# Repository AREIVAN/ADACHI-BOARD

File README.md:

# ADACHI-BOARD  
### Custom Embedded Control Board for Mini Sumo Robotics  
**ESP32-S3 | PCB Design | Motor Control | Embedded Systems**

---

## 📍 Overview

**ADACHI-BOARD** is a **custom-designed embedded control board** developed for **Mini Sumo robotic applications**, focused on **real-time control**, **compact PCB design**, and **competition-grade reliability**.

This project was created as part of my professional and academic development in **Robotics, Embedded Systems, and Industrial Electronics**, and it is intended to serve as both a **functional robotic platform** and a **technical portfolio project**.

---

## 🎯 Project Objectives

- Design a **compact and robust PCB** for competitive robotics
- Implement **reliable motor control** using discrete drivers
- Apply **best practices in embedded hardware design**
- Demonstrate skills in:
  - PCB design
  - Power regulation
  - Microcontroller integration
  - Robotics-oriented system architecture

---

## ⚙️ System Architecture

- **Main MCU:** ESP32-S3 Mini-1U  
- **Motor Control:** Dual DRV8871 DC motor drivers  
- **Sensors:** Support for up to 10 external sensors  
- **Actuators:** 2 servo outputs  
- **User Interface:** Hardware buttons for strategy selection  
- **Programming Interface:** TTL (UART)  

The board is designed to minimize latency and allow fast response times, which are critical in competitive robotics environments.

---

## 📐 Technical Specifications

| Feature | Description |
|------|------------|
| Board Size | 60 mm × 30 mm |
| Max Input Voltage | 24 V |
| MCU | ESP32-S3 Mini-1U |
| Motor Drivers | DRV8871 |
| Voltage Regulation | 5 V / 3.3 V |
| LEDs | SK0605 2427 |
| Programming | UART (TTL) |
| Target Application | Mini Sumo Robot |

---

## 🔘 Hardware Controls

- **RESET** – Microcontroller reset  
- **BOOT** – Programming mode access  
- **STRATEGY 1** – Strategy selection input  
- **STRATEGY 2** – Strategy selection input  

These buttons allow strategy changes without reflashing firmware, improving usability during competitions or testing.

---

## 🧠 Design Considerations

- Compact footprint optimized for Mini Sumo chassis
- Separation of power and logic domains
- Component selection focused on availability and reliability
- Design prepared for iterative improvement and future expansion

---

## 📂 Repository Structure

*(Structure may evolve as the project progresses)*

---

## 🚧 Project Status

- ✔ PCB design completed  
- ✔ Component selection validated  
- 🔄 Firmware development in progress  
- 🔄 Testing and optimization phase  

---

## 🔮 Planned Improvements

- Encoder feedback integration
- Power efficiency optimization
- Enhanced firmware architecture
- Step-by-step replication documentation
- Optional telemetry and data logging

---

## 👨‍💻 About the Author

**Areivan**  
Industrial Robotics Engineering Student  
Industrial Maintenance Technician  

- Experience in embedded systems and PCB design  
- Background in industrial automation and maintenance  
- Focused on robotics, electronics, and applied engineering  

🔗 GitHub: https://github.com/AREIVAN

---

## 📜 License & Usage

This project is intended for **educational and experimental purposes**.  
You may reference or reuse the design with proper credit to the author.

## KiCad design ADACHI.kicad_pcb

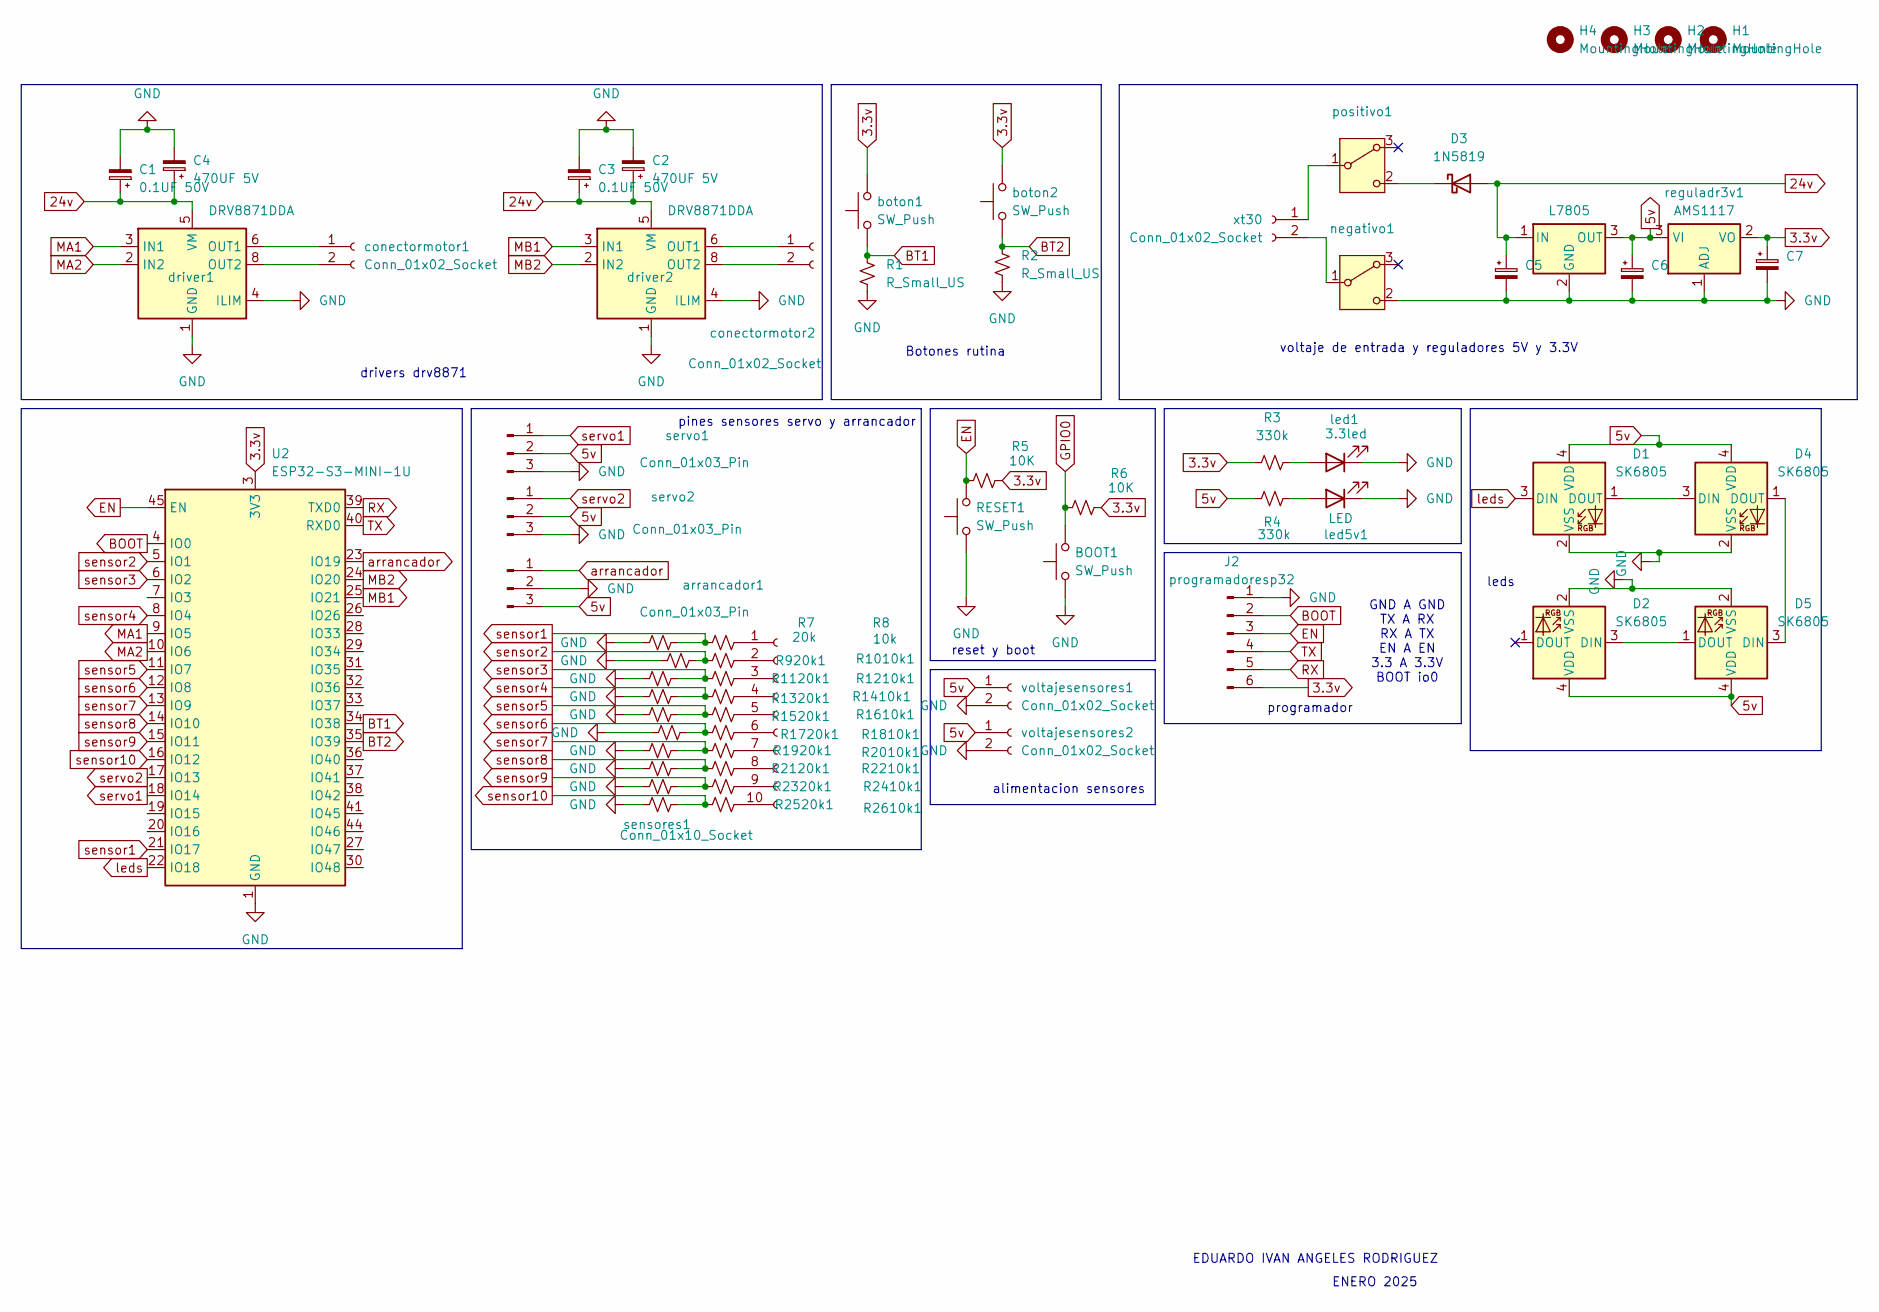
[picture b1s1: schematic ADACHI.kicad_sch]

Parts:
BOOT1: SW_Push; SW_Push_1P1T_NO_Vertical_Wuerth_434133025816
C1, C3: 0.1UF 50V; C_0603_1608Metric
C2, C4: 470UF 5V; C_1210_3225Metric
C5, C6, C7: C_0603_1608Metric
D1, D2, D4, D5: SK6805; LED_SK6805_PLCC4_2.4x2.7mm_P1.3mm
D3: 1N5819; D_DO-41_SOD81_P10.16mm_Horizontal
H1, H3, H4: MountingHole; MountingHole_2.2mm_M2_ISO7380_Pad_TopBottom
H2: MountingHole; MountingHole_2.2mm_M2_ISO14580_Pad_TopBottom
J2: programadoresp32; PinHeader_1x06_P2.54mm_Vertical
R1, R2: R_Small_US; R_0603_1608Metric
R3, R4: 330k; R_0603_1608Metric
R5, R6: 10K; R_0603_1608Metric
R7: 20k; R_0603_1608Metric
R8: 10k; R_0603_1608Metric
R920k1, R1010k1, R1120k1, R1210k1, R1320k1, R1410k1, R1520k1, R1610k1, R1720k1, R1810k1, R1920k1, R2010k1, R2120k1, R2210k1, R2320k1, R2410k1, R2520k1, R2610k1: R_0603_1608Metric
RESET1: SW_Push; SW_Push_1P1T_NO_Vertical_Wuerth_434133025816
U1: L7805; TO-252-2
U2: ESP32-S3-MINI-1U; ESP32-S2-MINI-1U
arrancador1: Conn_01x03_Pin; PinHeader_1x03_P2.54mm_Vertical
boton1, boton2: SW_Push; SW_Push_1P1T_NO_Vertical_Wuerth_434133025816
conectormotor1, conectormotor2: Conn_01x02_Socket; PinSocket_1x02_P2.54mm_Vertical
driver1, driver2: DRV8871DDA; Texas_HTSOP-8-1EP_3.9x4.9mm_P1.27mm_EP2.95x4.9mm_Mask2.4x3.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
led1: 3.3led; LED_0603_1608Metric
led5v1: LED; LED_0603_1608Metric
negativo1: SW_Slide-03_Wuerth-WS-SLTV_10x2.5x6.4_P2.54mm
positivo1: SW_Slide-03_Wuerth-WS-SLTV_10x2.5x6.4_P2.54mm
reguladr3v1: AMS1117; SOT-223-3_TabPin2
sensores1: Conn_01x10_Socket; PinHeader_1x10_P2.54mm_Vertical
servo1, servo2: Conn_01x03_Pin; PinHeader_1x03_P2.54mm_Vertical
voltajesensores1, voltajesensores2: Conn_01x02_Socket; PinHeader_1x02_P2.54mm_Vertical
xt30: Conn_01x02_Socket; PinHeader_1x02_P2.54mm_Vertical

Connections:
3.3v: C7.1, J2.6, R3.1, R5.2, R6.2, U2.3 (3V3), boton1.2, boton2.2, reguladr3v1.2 (VO)
5v: C6.1, D1.4 (VDD), D2.4 (VDD), D4.4 (VDD), D5.4 (VDD), R4.1, U1.3 (OUT), arrancador1.3, reguladr3v1.3 (VI), servo1.2, servo2.2, voltajesensores1.1, voltajesensores2.1
24v: C1.1, C2.1, C3.1, C4.1, C5.1, D3.2 (A), U1.1 (IN), driver1.5 (VM), driver2.5 (VM)
BOOT: J2.2, U2.4 (IO0)
BT1: R1.1, U2.34 (IO38), boton1.1
BT2: R2.1, U2.35 (IO39), boton2.1
EN: J2.3, R5.1, RESET1.2, U2.45 (EN)
GND: BOOT1.1, C1.2, C2.2, C3.2, C4.2, C5.2, C6.2, C7.2, D1.2 (VSS), D2.2 (VSS), D4.2 (VSS), D5.2 (VSS), J2.1, R1.2, R2.2, R7.2, R920k1.2, R1120k1.2, R1320k1.2, R1520k1.2, R1720k1.2, R1920k1.2, R2120k1.2, R2320k1.2, R2520k1.2, RESET1.1, U1.2 (GND), U2.1 (GND), U2.2 (GND), U2.42 (GND), U2.43 (GND), U2.46 (GND), U2.47 (GND), U2.48 (GND), U2.49 (GND), U2.50 (GND), U2.51 (GND), U2.52 (GND), U2.53 (GND), U2.54 (GND), U2.55 (GND), U2.56 (GND), U2.57 (GND), U2.58 (GND), U2.59 (GND), U2.60 (GND), U2.61 (GND), U2.62 (GND), U2.63 (GND), U2.64 (GND), U2.65 (GND), arrancador1.2, driver1.1 (GND), driver1.4 (ILIM), driver1.7 (GND), driver1.9 (GND), driver2.1 (GND), driver2.4 (ILIM), driver2.7 (GND), driver2.9 (GND), led1.1 (K), led5v1.1 (K), negativo1.2 (C), reguladr3v1.1 (ADJ), servo1.3, servo2.3, voltajesensores1.2, voltajesensores2.2
GPIO0: BOOT1.2, R6.1
MA1: U2.9 (IO5), driver1.3 (IN1)
MA2: U2.10 (IO6), driver1.2 (IN2)
MB1: U2.25 (IO21), driver2.3 (IN1)
MB2: U2.24 (IO20), driver2.2 (IN2)
unnamed: D1.1 (DOUT), D4.3 (DIN)
unnamed: D2.3 (DIN), D5.1 (DOUT)
unnamed: D3.1 (K), positivo1.2 (C)
unnamed: D4.1 (DOUT), D5.3 (DIN)
unnamed: conectormotor1.1, driver1.6 (OUT1)
unnamed: conectormotor1.2, driver1.8 (OUT2)
unnamed: conectormotor2.1, driver2.6 (OUT1)
unnamed: conectormotor2.2, driver2.8 (OUT2)
unnamed: R3.2, led1.2 (A)
unnamed: R4.2, led5v1.2 (A)
unnamed: negativo1.1 (B), xt30.2
unnamed: positivo1.1 (B), xt30.1
unnamed: R8.1, sensores1.1
unnamed: R1010k1.1, sensores1.2
unnamed: R1210k1.1, sensores1.3
unnamed: R1410k1.1, sensores1.4
unnamed: R1610k1.1, sensores1.5
unnamed: R1810k1.1, sensores1.6
unnamed: R2010k1.1, sensores1.7
unnamed: R2210k1.1, sensores1.8
unnamed: R2410k1.1, sensores1.9
unnamed: R2610k1.1, sensores1.10
RX: J2.5, U2.39 (TXD0)
TX: J2.4, U2.40 (RXD0)
arrancador: U2.23 (IO19), arrancador1.1
leds: D1.3 (DIN), U2.22 (IO18)
sensor1: R7.1, R8.2, U2.21 (IO17)
sensor2: R920k1.1, R1010k1.2, U2.5 (IO1)
sensor3: R1120k1.1, R1210k1.2, U2.6 (IO2)
sensor4: R1320k1.1, R1410k1.2, U2.8 (IO4)
sensor5: R1520k1.1, R1610k1.2, U2.11 (IO7)
sensor6: R1720k1.1, R1810k1.2, U2.12 (IO8)
sensor7: R1920k1.1, R2010k1.2, U2.13 (IO9)
sensor8: R2120k1.1, R2210k1.2, U2.14 (IO10)
sensor9: R2320k1.1, R2410k1.2, U2.15 (IO11)
sensor10: R2520k1.1, R2610k1.2, U2.16 (IO12)
servo1: U2.18 (IO14), servo1.1
servo2: U2.17 (IO13), servo2.1

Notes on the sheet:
reset y boot
pines sensores servo y arrancador
drivers drv8871
Botones rutina
ENERO 2025
programador
alimentacion sensores
GND A GND TX A RX RX A TX EN A EN 3.3 A 3.3V BOOT io0
leds
EDUARDO IVAN ANGELES RODRIGUEZ
voltaje de entrada y reguladores 5V y 3.3V

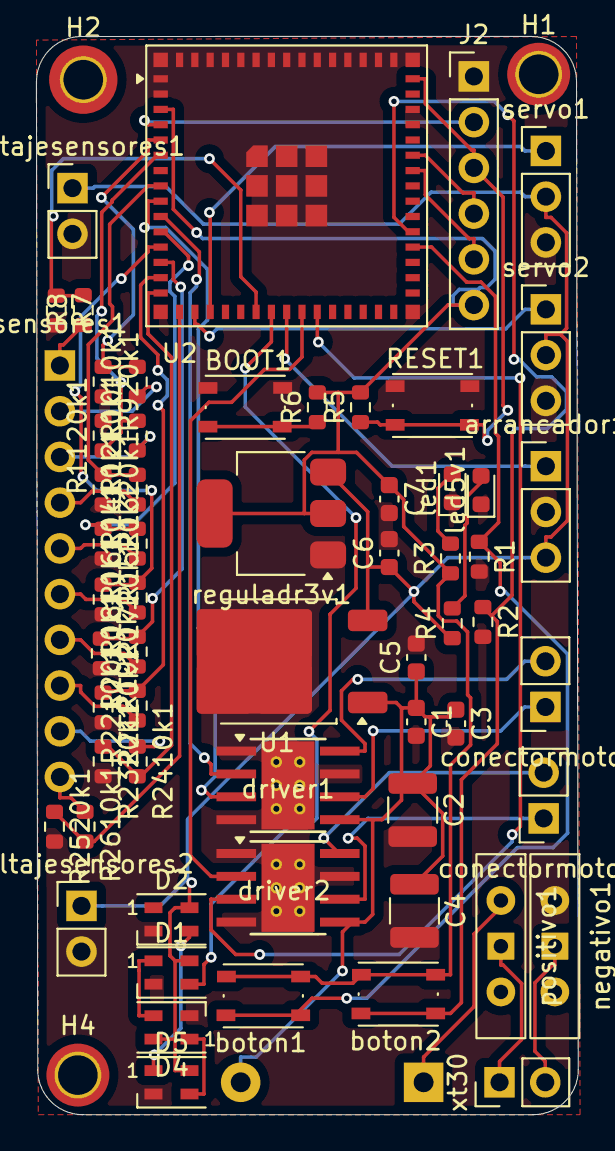
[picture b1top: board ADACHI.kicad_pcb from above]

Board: 2 copper layers, 30.1 x 59.9 mm, 64 parts (1 on the bottom side), 51 nets.

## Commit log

2025-01-30 README.md
2025-01-31 Add files via upload
    el esquematico y el 3d parecen correctos, falta enrutar
2025-02-01 Add files via upload
    primer enrutamiento terminado, falta checar si todas las conexiones son correctas y corregir el grosor de pistas donde hay mayor voltaje
2025-02-05 archivos kicad
    version final de la placa
2025-12-19 Revise README to enhance project documentation
    Expanded the README to include project overview, objectives, system architecture, technical specifications, hardware controls, design considerations, repository structure, project status, planned imp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
